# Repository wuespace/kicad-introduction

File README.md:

# KiCad Introduction

This project hosts the source files for a lecture about the ECAD tool
[KiCad](https://www.kicad.org/).

## Presentation Folder

The presentation is done with LaTex beamer. The style file is custom tailored to the WüSpace CI
guidelines (roboto and comfortaa font, correct accent purple) and can be swapped out if holding the lecture in a
different context.

## Tasks Folder

This folder is for KiCAD project files that correspond to the lecture. Currently there's only the
project `baby-steps` but more can be added for further advanced lectures.

## License
CC BY-SA 4.0

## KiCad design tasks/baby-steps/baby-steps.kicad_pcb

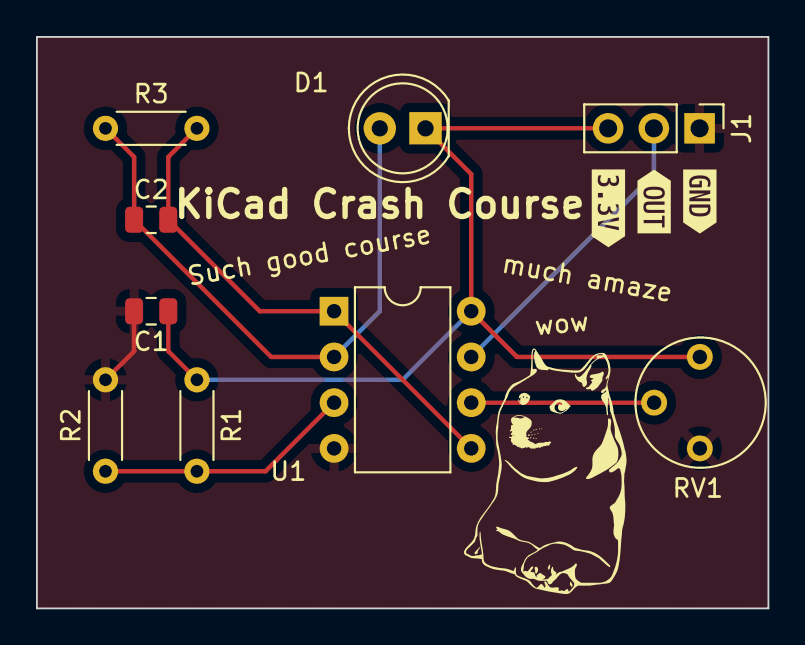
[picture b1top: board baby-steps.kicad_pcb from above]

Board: 2 copper layers, 40.6 x 31.8 mm, 12 parts (0 on the bottom side), 7 nets.

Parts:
C1, C2: C; C_0805_2012Metric
D1: D; LED_D5.0mm
J1: Conn_01x03; PinHeader_1x03_P2.54mm_Vertical
R1, R2, R3: R; R_Axial_DIN0204_L3.6mm_D1.6mm_P5.08mm_Horizontal
RV1: R_Potentiometer; Potentiometer_Vishay_T7-YA_Single_Vertical
U1: LMC6482; DIP-8_W7.62mm
kibuzzard-653A80D4: G***; kibuzzard-653A80D4
kibuzzard-653A80DD: G***; kibuzzard-653A80DD
kibuzzard-653A80F5: G***; kibuzzard-653A80F5

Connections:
+3.3V: C1.1, D1.1 (K), J1.3, R1.1, RV1.1, U1.8 (V+)
/Vout: J1.2, U1.7
GND: C1.2, J1.1, R2.2, RV1.3, U1.4 (V-)
unnamed: C2.1, D1.2 (A), R3.1, U1.2 (-)
unnamed: R1.2, R2.1, U1.3 (+)
unnamed: C2.2, R3.2, U1.1, U1.5 (+)
unnamed: RV1.2, U1.6 (-)

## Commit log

2023-12-07 Add citation.cff
2023-12-07 move form to own folder
2023-12-07 Create LICENSE
